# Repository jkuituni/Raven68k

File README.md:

# Raven68k
Raven 68k is a simple Motorola 68k family based single board computer. The machine will serve as a learning tool
for building a 68k based machines for learning on how to interface various chips and add on expansions for the
architecture. It is also aimed to be a platform for learning on how to write firmware and operating system level
code and how to implement the required logic in VHDL code to tie in all of the functionality required. We are
interested on eventually getting Linux up and running on the hardware as the Linux/m68k is still maintained and
it supports many of the basic building blocks.

The project will be documented to a blog along with datasheets of all the components used.

## Folder Structure
*datasheets/* -- The datasheets of the components used in various revisions of Raven.

*firmware/* - ROM images to boot and initialize the system.

*software/* - S68 programs that can be loaded from the firmware. Many of these are built with [EASy68k](http://easy68k.com/).

*hardware/* -- KiCAD schematics and other files as well as VHDL code for the CPLD are located here.

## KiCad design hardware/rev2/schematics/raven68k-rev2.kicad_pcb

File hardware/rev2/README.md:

# Raven68k - Revision 2

The specifications for the revision 2 version of Raven68k are as follows:

- Motorola 68010 CPU
- 64kB of EEPROM for bootstrapping the Linux
- Single 72pin SIMM socket for RAM. Upto 16MB supported.
- Motorola 68681 DUART with USB adapter on one UART and max233 on other
- Dallas DS12887A Real Time Clock
- Xilinx XC9572XL CPLD as system glue logic.

The revision 2 of Raven is intended as a minor improvement and bug fix version. Most likely no further revisions will be made and work will continue in a higher spec follow-up computer.

## Folder structure

*schematic/* - KiCad schematics for this revision.

*vhdl/* - The VHDL source for the CPLD that manages most of the TTL logic present and implements the DRAM controller. 

*xilinx/* - The ISE WebPack (14.2) project itself, which targets a QFP100 XC9572XL.

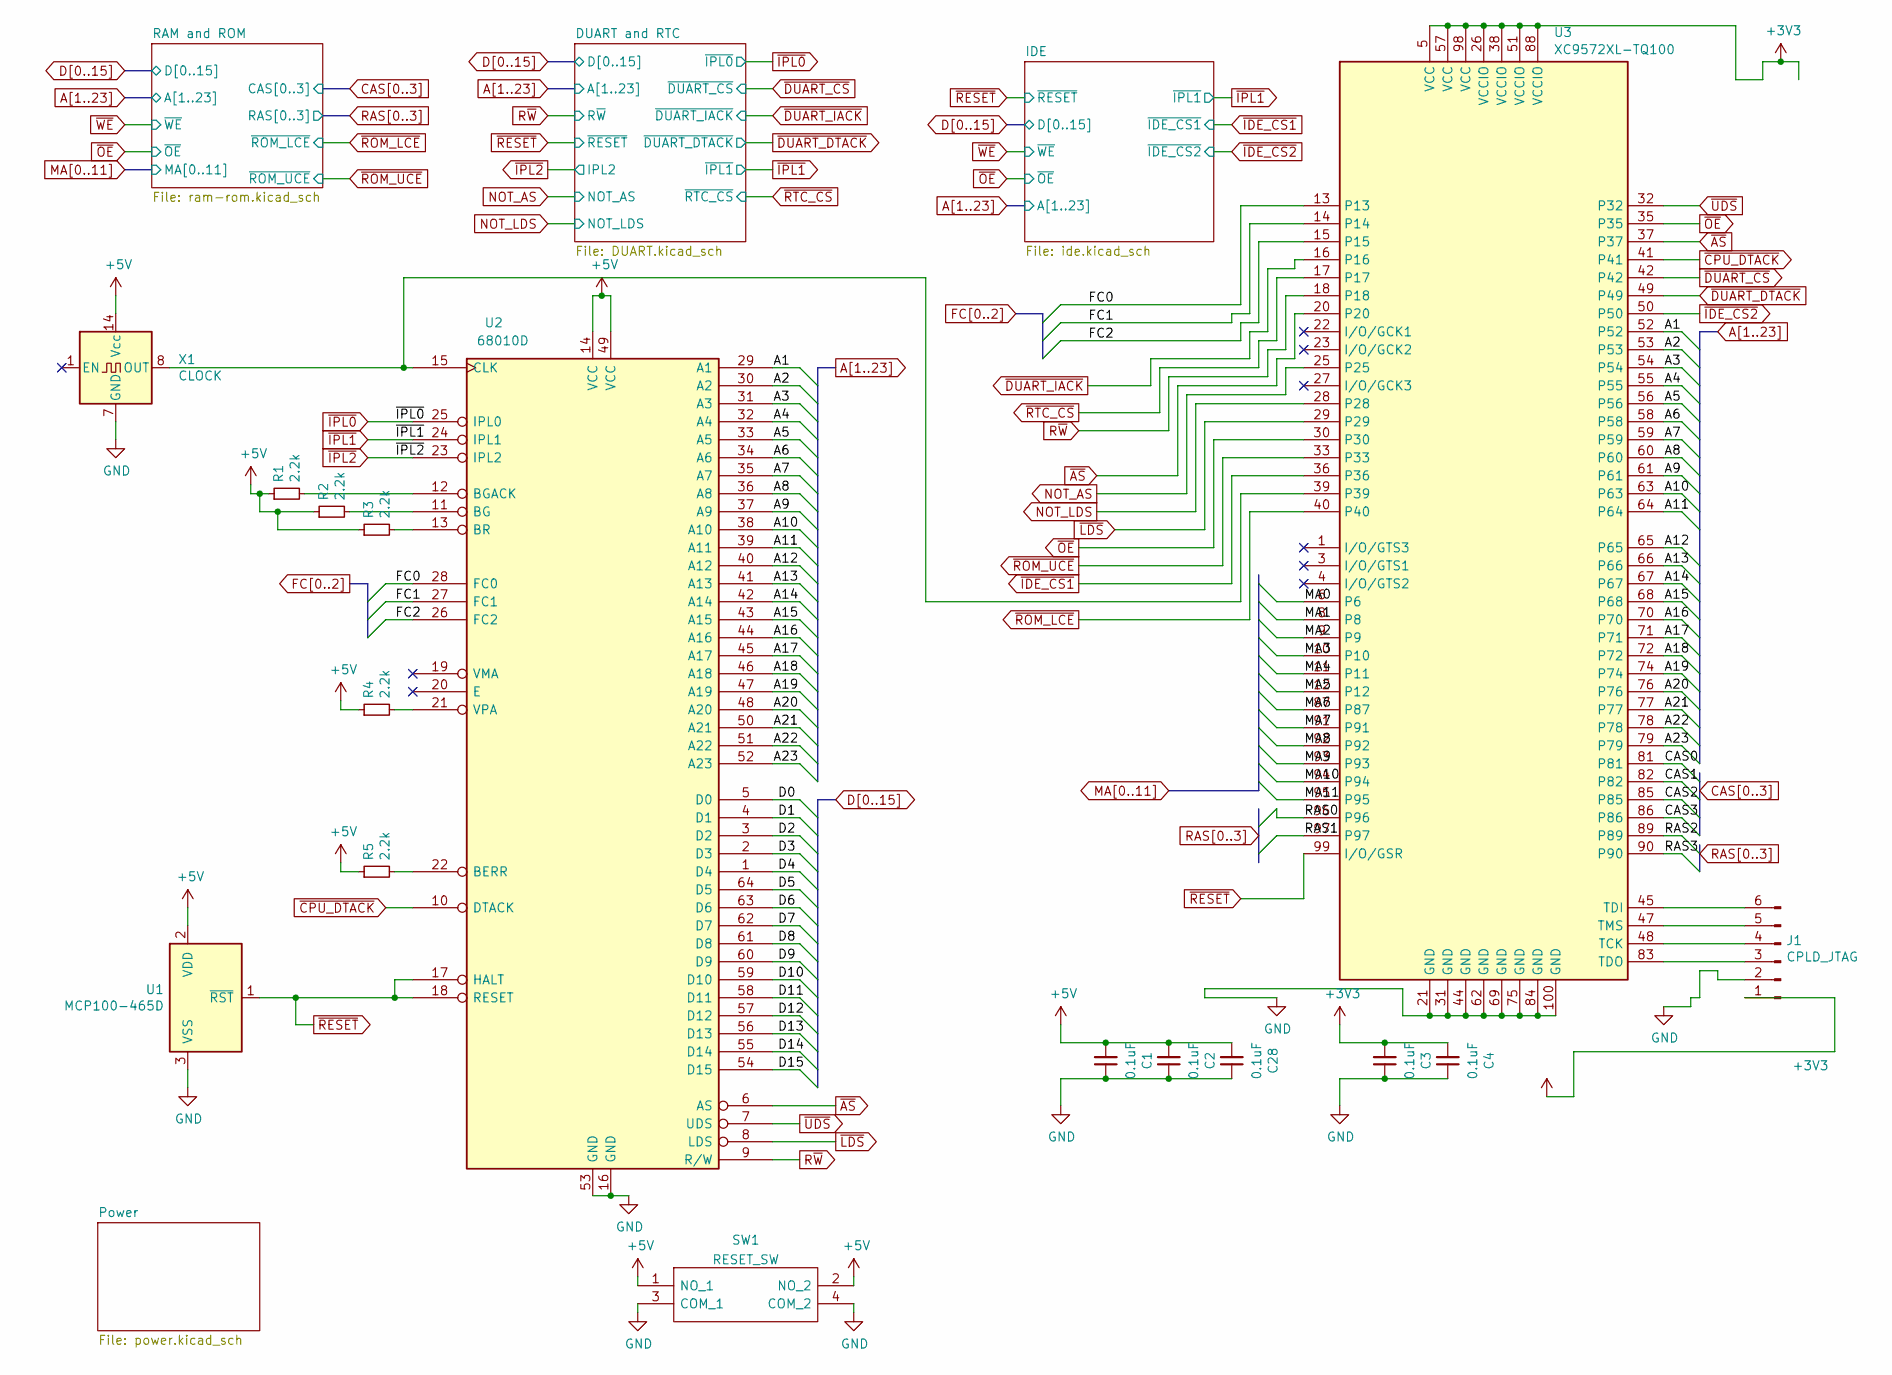
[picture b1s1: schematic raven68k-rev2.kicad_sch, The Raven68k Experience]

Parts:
C1, C2, C3, C4, C28: 0.1uF; C_1206_3216Metric_Pad1.33x1.80mm_HandSolder; LCSC C24497
J1: CPLD_JTAG; PinHeader_1x06_P2.54mm_Vertical
R1, R2, R3, R4, R5: 2.2k; R_1206_3216Metric_Pad1.30x1.75mm_HandSolder
SW1: RESET_SW; TS0266170BK160SCRD; Manufacturer_Part_Number TS02-66-170-BK-160-SCR-D
U1: MCP100-465D; TO-92L_HandSolder
U2: 68010D; DIP-64_W25.4mm_Socket_LongPads
U3: XC9572XL-TQ100; TQFP-100_14x14mm_P0.5mm
X1: CLOCK; Oscillator_DIP-14_LargePads

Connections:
+3V3: C3.2, C4.2, J1.1, U3.5 (VCC), U3.26 (VCCIO), U3.38 (VCCIO), U3.51 (VCCIO), U3.57 (VCC), U3.88 (VCCIO), U3.98 (VCC); also elsewhere on the board
+5V: C1.2, C2.2, C28.2, R1.1, R2.1, R3.1, R4.1, R5.1, SW1.1 (NO_1), SW1.2 (NO_2), U1.2 (VDD), U2.14 (VCC), U2.49 (VCC), X1.14 (Vcc); also elsewhere on the board
A1: U2.29 (A1), U3.52; also elsewhere on the board
A2: U2.30 (A2), U3.53; also elsewhere on the board
A3: U2.31 (A3), U3.54; also elsewhere on the board
A4: U2.32 (A4), U3.55; also elsewhere on the board
A5: U2.33 (A5), U3.56; also elsewhere on the board
A6: U2.34 (A6), U3.58; also elsewhere on the board
A7: U2.35 (A7), U3.59; also elsewhere on the board
A8: U2.36 (A8), U3.60; also elsewhere on the board
A9: U2.37 (A9), U3.61; also elsewhere on the board
A10: U2.38 (A10), U3.63; also elsewhere on the board
A11: U2.39 (A11), U3.64; also elsewhere on the board
A12: U2.40 (A12), U3.65; also elsewhere on the board
A13: U2.41 (A13), U3.66; also elsewhere on the board
A14: U2.42 (A14), U3.67; also elsewhere on the board
A15: U2.43 (A15), U3.68; also elsewhere on the board
A16: U2.44 (A16), U3.70
A17: U2.45 (A17), U3.71
A18: U2.46 (A18), U3.72
A19: U2.47 (A19), U3.74
A20: U2.48 (A20), U3.76
A21: U2.50 (A21), U3.77
A22: U2.51 (A22), U3.78
A23: U2.52 (A23), U3.79
CAS0: U3.81; also elsewhere on the board
CAS1: U3.82; also elsewhere on the board
CAS2: U3.85; also elsewhere on the board
CAS3: U3.86; also elsewhere on the board
D0: U2.5 (D0); also elsewhere on the board
D1: U2.4 (D1); also elsewhere on the board
D2: U2.3 (D2); also elsewhere on the board
D3: U2.2 (D3); also elsewhere on the board
D4: U2.1 (D4); also elsewhere on the board
D5: U2.64 (D5); also elsewhere on the board
D6: U2.63 (D6); also elsewhere on the board
D7: U2.62 (D7); also elsewhere on the board
D8: U2.61 (D8); also elsewhere on the board
D9: U2.60 (D9); also elsewhere on the board
D10: U2.59 (D10); also elsewhere on the board
D11: U2.58 (D11); also elsewhere on the board
D12: U2.57 (D12); also elsewhere on the board
D13: U2.56 (D13); also elsewhere on the board
D14: U2.55 (D14); also elsewhere on the board
D15: U2.54 (D15); also elsewhere on the board
FC0: U2.28 (FC0), U3.13
FC1: U2.27 (FC1), U3.14
FC2: U2.26 (FC2), U3.15
GND: C1.1, C2.1, C3.1, C4.1, C28.1, J1.2, SW1.3 (COM_1), SW1.4 (COM_2), U1.3 (VSS), U2.16 (GND), U2.53 (GND), U3.21 (GND), U3.31 (GND), U3.44 (GND), U3.62 (GND), U3.69 (GND), U3.75 (GND), U3.84 (GND), U3.100 (GND), X1.7 (GND); also elsewhere on the board
MA0: U3.6; also elsewhere on the board
MA1: U3.8; also elsewhere on the board
MA2: U3.9; also elsewhere on the board
MA3: U3.10; also elsewhere on the board
MA4: U3.11; also elsewhere on the board
MA5: U3.12; also elsewhere on the board
MA6: U3.87; also elsewhere on the board
MA7: U3.91; also elsewhere on the board
MA8: U3.92; also elsewhere on the board
MA9: U3.93; also elsewhere on the board
MA10: U3.94; also elsewhere on the board
MA11: U3.95; also elsewhere on the board
NOT_AS: U3.25; also elsewhere on the board
NOT_LDS: U3.28; also elsewhere on the board
unnamed: J1.3, U3.83 (TDO)
unnamed: J1.4, U3.48 (TCK)
unnamed: J1.5, U3.47 (TMS)
unnamed: J1.6, U3.45 (TDI)
unnamed: R5.2, U2.22 (BERR)
unnamed: R2.2, U2.11 (BG)
unnamed: R1.2, U2.12 (BGACK)
unnamed: R3.2, U2.13 (BR)
unnamed: U2.15 (CLK), U3.39, X1.8 (OUT)
unnamed: R4.2, U2.21 (VPA)
RAS0: U3.96; also elsewhere on the board
RAS1: U3.97; also elsewhere on the board
RAS2: U3.89; also elsewhere on the board
RAS3: U3.90; also elsewhere on the board
R~W: U2.9 (R/W), U3.18; also elsewhere on the board
~AS: U2.6 (AS), U3.20, U3.37
~CPU_DTACK: U2.10 (DTACK), U3.41
~DUART_CS: U3.42; also elsewhere on the board
~DUART_DTACK: U3.49; also elsewhere on the board
~DUART_IACK: U3.16; also elsewhere on the board
~IDE_CS1: U3.36; also elsewhere on the board
~IDE_CS2: U3.50; also elsewhere on the board
~IPL0: U2.25 (IPL0); also elsewhere on the board
~IPL1: U2.24 (IPL1); also elsewhere on the board
~IPL2: U2.23 (IPL2); also elsewhere on the board
~LDS: U2.8 (LDS), U3.29
~OE: U3.30, U3.35; also elsewhere on the board
~RESET: U1.1 (~RST), U2.17 (HALT), U2.18 (RESET), U3.99 (I/O/GSR); also elsewhere on the board
~ROM_LCE: U3.40; also elsewhere on the board
~ROM_UCE: U3.33; also elsewhere on the board
~RTC_CS: U3.17; also elsewhere on the board
~UDS: U2.7 (UDS), U3.32

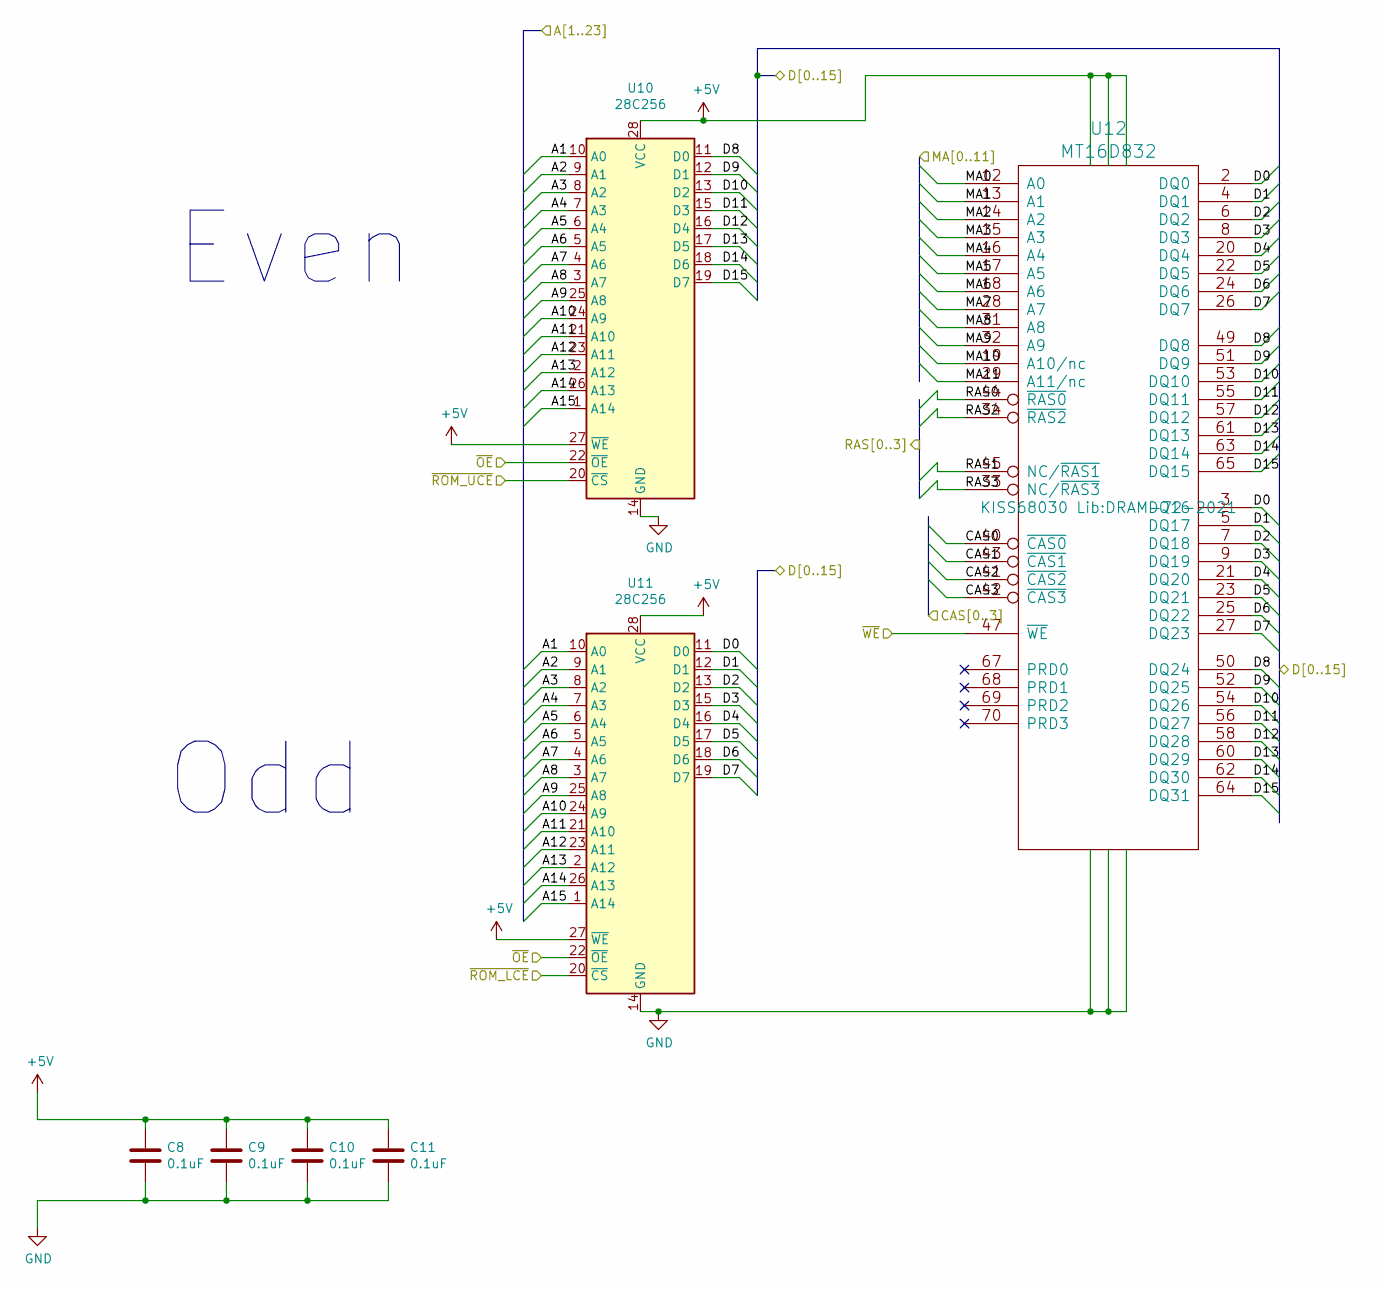
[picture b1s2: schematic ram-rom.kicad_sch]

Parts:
C8, C9, C10, C11: 0.1uF; C_1206_3216Metric_Pad1.33x1.80mm_HandSolder; LCSC C24497
U10, U11: 28C256; DIP-28_W15.24mm_Socket_LongPads
U12: MT16D832; DRAM-72-2021

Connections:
+5V: C8.1, C9.1, C10.1, C11.1, U10.27 (~WE), U10.28 (VCC), U11.27 (~WE), U11.28 (VCC), U12.10 (VCC), U12.30 (VCC), U12.59 (VCC); also elsewhere on the board
A1: U10.10 (A0), U11.10 (A0); also elsewhere on the board
A2: U10.9 (A1), U11.9 (A1); also elsewhere on the board
A3: U10.8 (A2), U11.8 (A2); also elsewhere on the board
A4: U10.7 (A3), U11.7 (A3); also elsewhere on the board
A5: U10.6 (A4), U11.6 (A4); also elsewhere on the board
A6: U10.5 (A5), U11.5 (A5); also elsewhere on the board
A7: U10.4 (A6), U11.4 (A6); also elsewhere on the board
A8: U10.3 (A7), U11.3 (A7); also elsewhere on the board
A9: U10.25 (A8), U11.25 (A8); also elsewhere on the board
A10: U10.24 (A9), U11.24 (A9); also elsewhere on the board
A11: U10.21 (A10), U11.21 (A10); also elsewhere on the board
A12: U10.23 (A11), U11.23 (A11); also elsewhere on the board
A13: U10.2 (A12), U11.2 (A12); also elsewhere on the board
A14: U10.26 (A13), U11.26 (A13); also elsewhere on the board
A15: U10.1 (A14), U11.1 (A14); also elsewhere on the board
CAS0: U12.40 (~CAS0); also elsewhere on the board
CAS1: U12.43 (~CAS1); also elsewhere on the board
CAS2: U12.41 (~CAS2); also elsewhere on the board
CAS3: U12.42 (~CAS3); also elsewhere on the board
D0: U11.11 (D0), U12.2 (DQ0), U12.3 (DQ16); also elsewhere on the board
D1: U11.12 (D1), U12.4 (DQ1), U12.5 (DQ17); also elsewhere on the board
D2: U11.13 (D2), U12.6 (DQ2), U12.7 (DQ18); also elsewhere on the board
D3: U11.15 (D3), U12.8 (DQ3), U12.9 (DQ19); also elsewhere on the board
D4: U11.16 (D4), U12.20 (DQ4), U12.21 (DQ20); also elsewhere on the board
D5: U11.17 (D5), U12.22 (DQ5), U12.23 (DQ21); also elsewhere on the board
D6: U11.18 (D6), U12.24 (DQ6), U12.25 (DQ22); also elsewhere on the board
D7: U11.19 (D7), U12.26 (DQ7), U12.27 (DQ23); also elsewhere on the board
D8: U10.11 (D0), U12.49 (DQ8), U12.50 (DQ24); also elsewhere on the board
D9: U10.12 (D1), U12.51 (DQ9), U12.52 (DQ25); also elsewhere on the board
D10: U10.13 (D2), U12.53 (DQ10), U12.54 (DQ26); also elsewhere on the board
D11: U10.15 (D3), U12.55 (DQ11), U12.56 (DQ27); also elsewhere on the board
D12: U10.16 (D4), U12.57 (DQ12), U12.58 (DQ28); also elsewhere on the board
D13: U10.17 (D5), U12.60 (DQ29), U12.61 (DQ13); also elsewhere on the board
D14: U10.18 (D6), U12.62 (DQ30), U12.63 (DQ14); also elsewhere on the board
D15: U10.19 (D7), U12.64 (DQ31), U12.65 (DQ15); also elsewhere on the board
GND: C8.2, C9.2, C10.2, C11.2, U10.14 (GND), U11.14 (GND), U12.1 (GND), U12.39 (GND), U12.72 (GND); also elsewhere on the board
MA0: U12.12 (A0); also elsewhere on the board
MA1: U12.13 (A1); also elsewhere on the board
MA2: U12.14 (A2); also elsewhere on the board
MA3: U12.15 (A3); also elsewhere on the board
MA4: U12.16 (A4); also elsewhere on the board
MA5: U12.17 (A5); also elsewhere on the board
MA6: U12.18 (A6); also elsewhere on the board
MA7: U12.28 (A7); also elsewhere on the board
MA8: U12.31 (A8); also elsewhere on the board
MA9: U12.32 (A9); also elsewhere on the board
MA10: U12.19 (A10/nc); also elsewhere on the board
MA11: U12.29 (A11/nc); also elsewhere on the board
RAS0: U12.44 (~RAS0); also elsewhere on the board
RAS1: U12.45 (NC/~RAS1); also elsewhere on the board
RAS2: U12.34 (~RAS2); also elsewhere on the board
RAS3: U12.33 (NC/~RAS3); also elsewhere on the board
~OE: U10.22 (~OE), U11.22 (~OE); also elsewhere on the board
~ROM_LCE: U11.20 (~CS); also elsewhere on the board
~ROM_UCE: U10.20 (~CS); also elsewhere on the board
~WE: U12.47 (~WE); also elsewhere on the board

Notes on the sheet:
Even
Odd

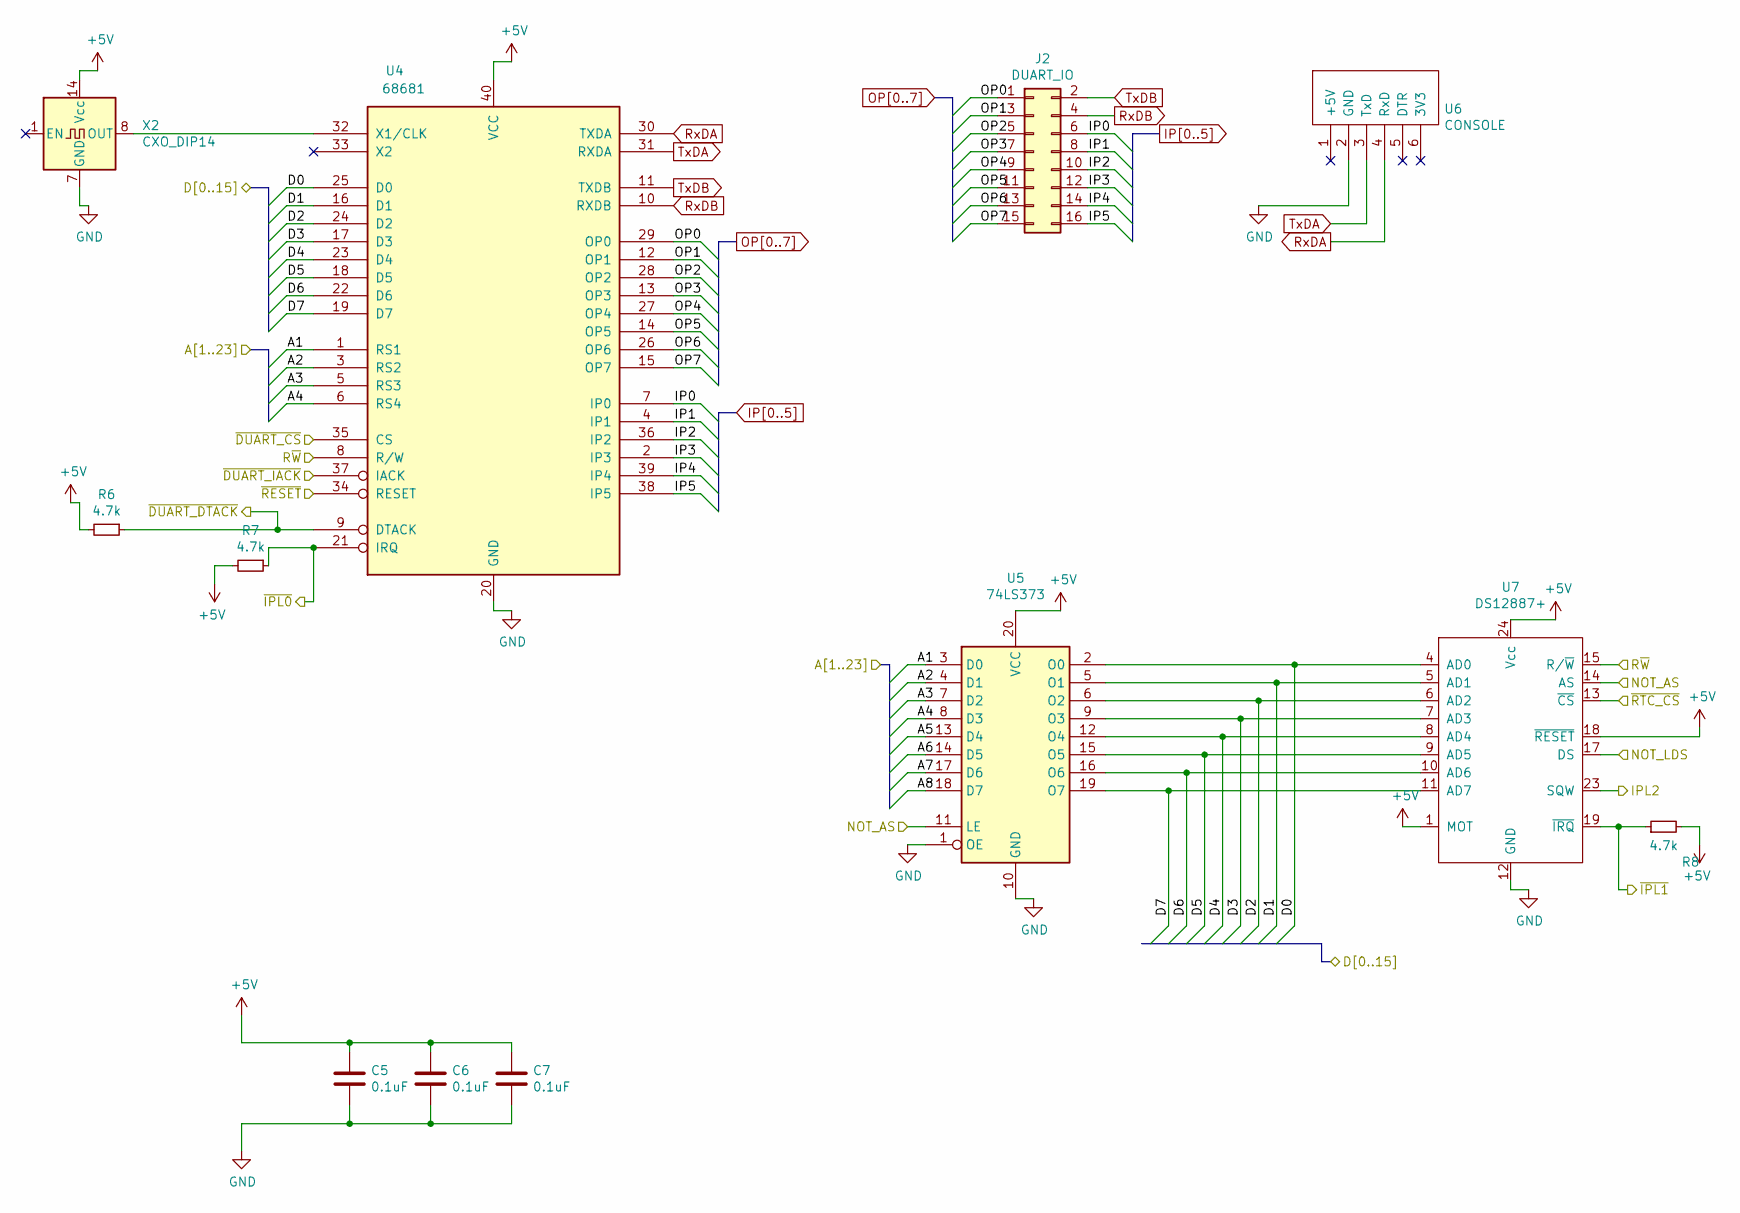
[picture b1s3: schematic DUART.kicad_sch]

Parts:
C5, C6, C7: 0.1uF; C_1206_3216Metric_Pad1.33x1.80mm_HandSolder; LCSC C24497
J2: DUART_IO; PinHeader_2x08_P2.54mm_Vertical
R6, R7, R8: 4.7k; R_1206_3216Metric_Pad1.30x1.75mm_HandSolder
U4: 68681; DIP-40_W25.4mm_Socket_LongPads
U5: 74LS373; DIP-20_W7.62mm_Socket_LongPads
U6: CONSOLE; PinHeader_1x06_P2.54mm_Vertical
U7: DS12887+; DIP-24_W15.24mm_Socket_LongPads
X2: CXO_DIP14; Oscillator_DIP-14_LargePads

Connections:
+5V: C5.1, C6.1, C7.1, R6.2, R7.2, R8.2, U4.40 (VCC), U5.20 (VCC), U7.1 (MOT), U7.18 (~RESET), U7.24 (Vcc), X2.14 (Vcc); also elsewhere on the board
A1: U4.1 (RS1), U5.3 (D0); also elsewhere on the board
A2: U4.3 (RS2), U5.4 (D1); also elsewhere on the board
A3: U4.5 (RS3), U5.7 (D2); also elsewhere on the board
A4: U4.6 (RS4), U5.8 (D3); also elsewhere on the board
A5: U5.13 (D4); also elsewhere on the board
A6: U5.14 (D5); also elsewhere on the board
A7: U5.17 (D6); also elsewhere on the board
A8: U5.18 (D7); also elsewhere on the board
D0: U4.25 (D0), U5.2 (O0), U7.4 (AD0); also elsewhere on the board
D1: U4.16 (D1), U5.5 (O1), U7.5 (AD1); also elsewhere on the board
D2: U4.24 (D2), U5.6 (O2), U7.6 (AD2); also elsewhere on the board
D3: U4.17 (D3), U5.9 (O3), U7.7 (AD3); also elsewhere on the board
D4: U4.23 (D4), U5.12 (O4), U7.8 (AD4); also elsewhere on the board
D5: U4.18 (D5), U5.15 (O5), U7.9 (AD5); also elsewhere on the board
D6: U4.22 (D6), U5.16 (O6), U7.10 (AD6); also elsewhere on the board
D7: U4.19 (D7), U5.19 (O7), U7.11 (AD7); also elsewhere on the board
GND: C5.2, C6.2, C7.2, U4.20 (GND), U5.1 (OE), U5.10 (GND), U6.2 (GND), U7.12 (GND), X2.7 (GND); also elsewhere on the board
IP0: J2.6, U4.7 (IP0)
IP1: J2.8, U4.4 (IP1)
IP2: J2.10, U4.36 (IP2)
IP3: J2.12, U4.2 (IP3)
IP4: J2.14, U4.39 (IP4)
IP5: J2.16, U4.38 (IP5)
NOT_AS: U5.11 (LE), U7.14 (AS); also elsewhere on the board
NOT_LDS: U7.17 (DS); also elsewhere on the board
unnamed: U4.32 (X1/CLK), X2.8 (OUT)
OP0: J2.1, U4.29 (OP0)
OP1: J2.3, U4.12 (OP1)
OP2: J2.5, U4.28 (OP2)
OP3: J2.7, U4.13 (OP3)
OP4: J2.9, U4.27 (OP4)
OP5: J2.11, U4.14 (OP5)
OP6: J2.13, U4.26 (OP6)
OP7: J2.15, U4.15 (OP7)
RxDA: U4.30 (TXDA), U6.4 (RxD)
RxDB: J2.4, U4.10 (RXDB)
R~W: U4.8 (R/W), U7.15 (R/~W); also elsewhere on the board
TxDA: U4.31 (RXDA), U6.3 (TxD)
TxDB: J2.2, U4.11 (TXDB)
~DUART_CS: U4.35 (CS); also elsewhere on the board
~DUART_DTACK: R6.1, U4.9 (DTACK); also elsewhere on the board
~DUART_IACK: U4.37 (IACK); also elsewhere on the board
~IPL0: R7.1, U4.21 (IRQ); also elsewhere on the board
~IPL1: R8.1, U7.19 (~IRQ); also elsewhere on the board
~IPL2: U7.23 (SQW); also elsewhere on the board
~RESET: U4.34 (RESET); also elsewhere on the board
~RTC_CS: U7.13 (~CS); also elsewhere on the board

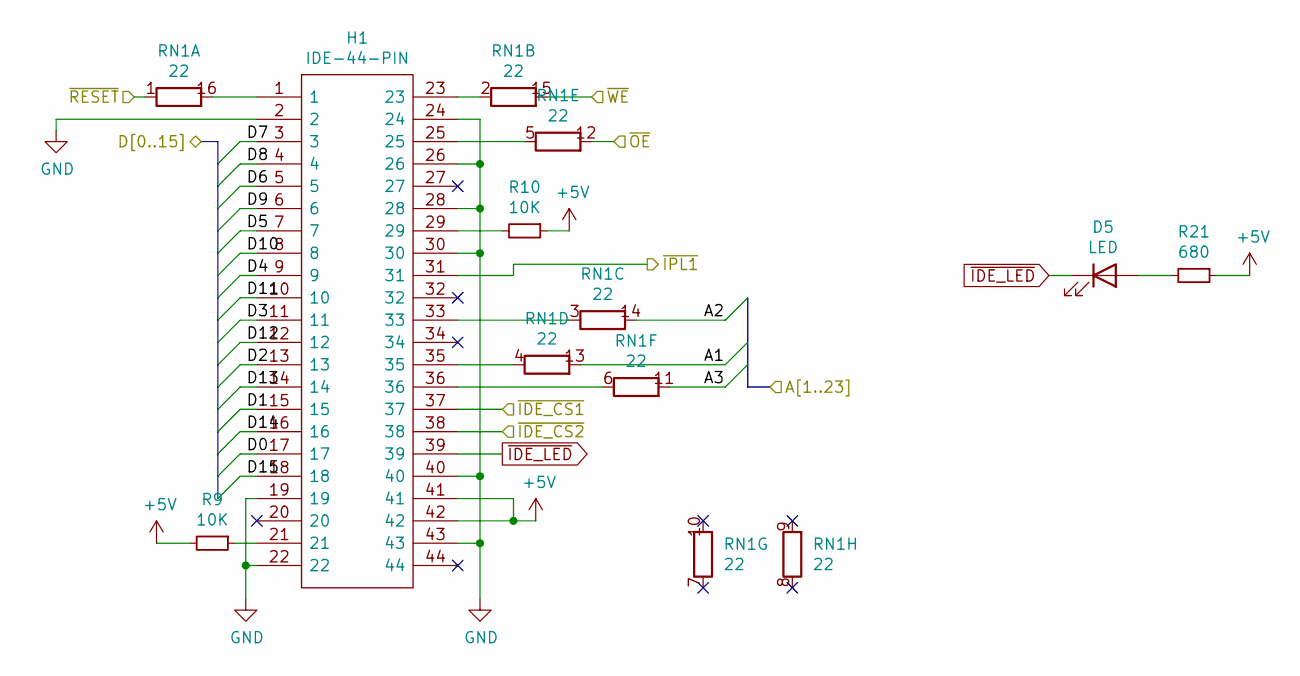
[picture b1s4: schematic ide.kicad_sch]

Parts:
D5: LED; LED_D3.0mm
H1: IDE-44-PIN; SHDR44W55P200_2X22_4665X630X640P; Manufacturer_Part_Number 57102-G06-22LF
R9, R10: 10K; R_1206_3216Metric_Pad1.30x1.75mm_HandSolder
R21: 680; R_1206_3216Metric_Pad1.30x1.75mm_HandSolder
RN1: 22; DIP-16_W7.62mm_Socket_LongPads

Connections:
+5V: H1.41, H1.42, R9.2, R10.1, R21.1; also elsewhere on the board
A1: RN1.13 (R4.2); also elsewhere on the board
A2: RN1.14 (R3.2); also elsewhere on the board
A3: RN1.11 (R6.2); also elsewhere on the board
D0: H1.17; also elsewhere on the board
D1: H1.15; also elsewhere on the board
D2: H1.13; also elsewhere on the board
D3: H1.11; also elsewhere on the board
D4: H1.9; also elsewhere on the board
D5: H1.7; also elsewhere on the board
D6: H1.5; also elsewhere on the board
D7: H1.3; also elsewhere on the board
D8: H1.4; also elsewhere on the board
D9: H1.6; also elsewhere on the board
D10: H1.8; also elsewhere on the board
D11: H1.10; also elsewhere on the board
D12: H1.12; also elsewhere on the board
D13: H1.14; also elsewhere on the board
D14: H1.16; also elsewhere on the board
D15: H1.18; also elsewhere on the board
GND: H1.2, H1.19, H1.22, H1.24, H1.26, H1.28, H1.30, H1.40, H1.43; also elsewhere on the board
unnamed: D5.2 (A), R21.2
unnamed: H1.21, R9.1
unnamed: H1.29, R10.2
unnamed: H1.1, RN1.16 (R1.2)
unnamed: H1.23, RN1.2 (R2.1)
unnamed: H1.33, RN1.3 (R3.1)
unnamed: H1.35, RN1.4 (R4.1)
unnamed: H1.25, RN1.5 (R5.1)
unnamed: H1.36, RN1.6 (R6.1)
~IDE_CS1: H1.37; also elsewhere on the board
~IDE_CS2: H1.38; also elsewhere on the board
~IDE_LED: D5.1 (K), H1.39
~IPL1: H1.31; also elsewhere on the board
~OE: RN1.12 (R5.2); also elsewhere on the board
~RESET: RN1.1 (R1.1); also elsewhere on the board
~WE: RN1.15 (R2.2); also elsewhere on the board

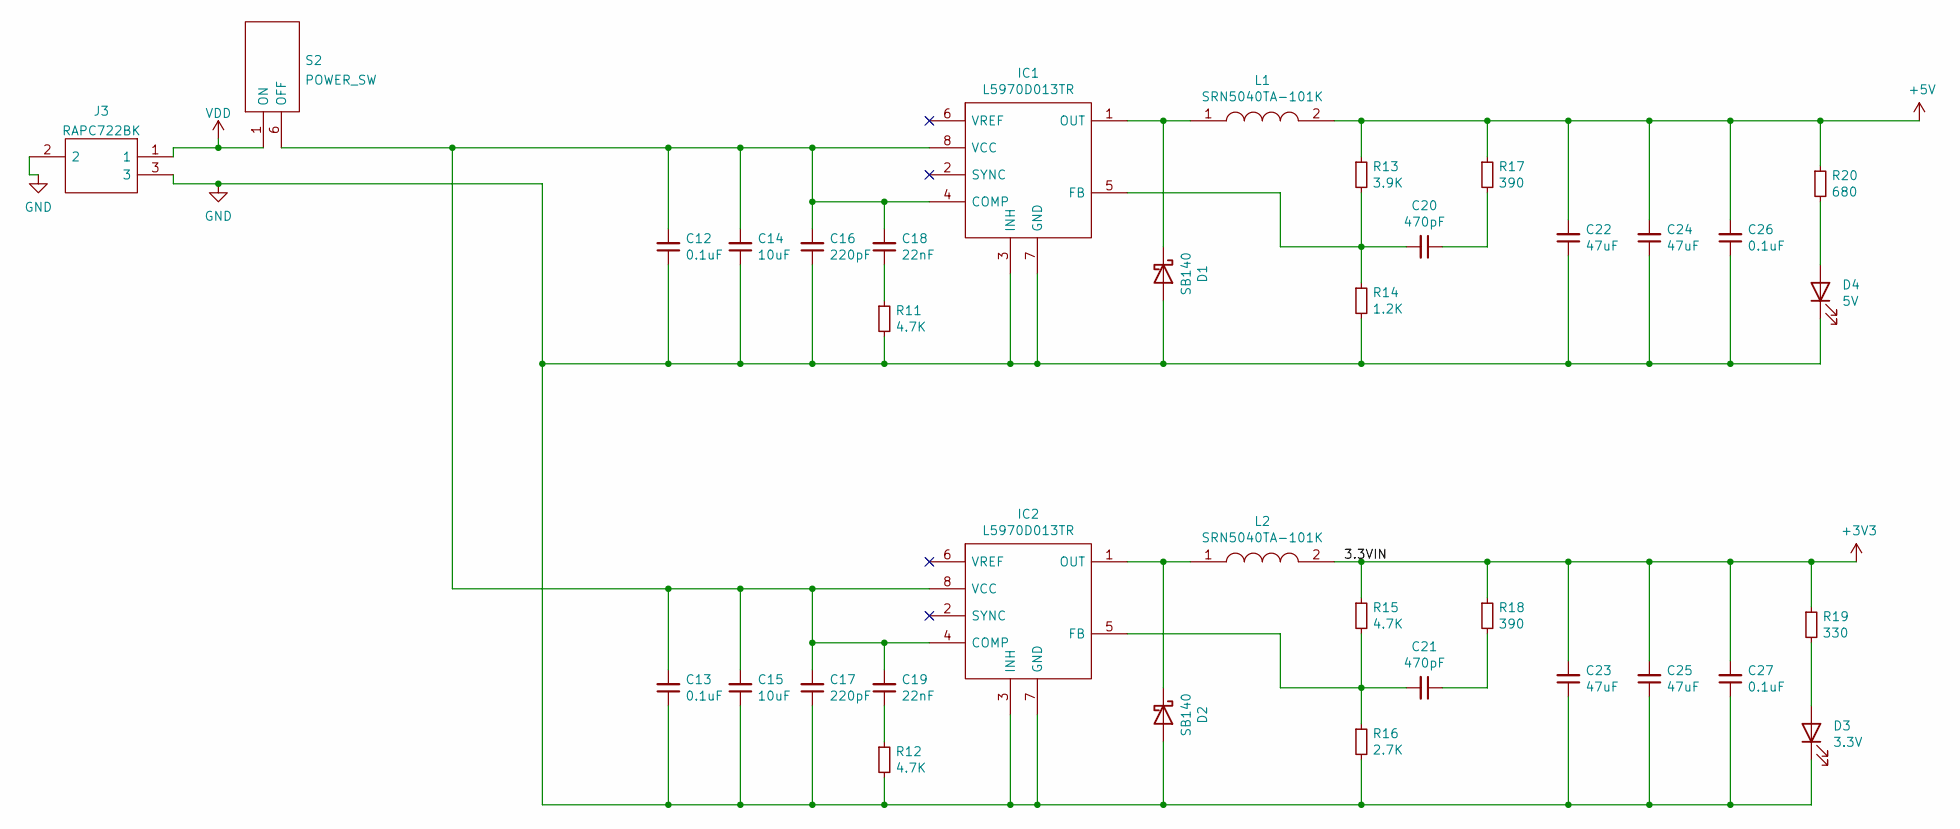
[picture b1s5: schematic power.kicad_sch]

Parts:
C12, C13, C26, C27: 0.1uF; C_1206_3216Metric_Pad1.33x1.80mm_HandSolder; LCSC C24497
C14, C15: 10uF; C_1206_3216Metric_Pad1.33x1.80mm_HandSolder; LCSC C13585
C16, C17: 220pF; C_1206_3216Metric_Pad1.33x1.80mm_HandSolder; LCSC C1854
C18, C19: 22nF; C_1206_3216Metric_Pad1.33x1.80mm_HandSolder; LCSC C97929
C20, C21: 470pF; C_1206_3216Metric_Pad1.33x1.80mm_HandSolder; LCSC C1868
C22, C23, C24, C25: 47uF; C_1206_3216Metric_Pad1.33x1.80mm_HandSolder
D1, D2: SB140; D_1206_3216Metric_Pad1.42x1.75mm_HandSolder
D3: 3.3V; LED_D3.0mm
D4: 5V; LED_D3.0mm
IC1, IC2: L5970D013TR; SO-8_5.3x6.2mm_P1.27mm; Manufacturer_Part_Number L5970D013TR; Mouser Part Number 511-L5970D013TR
J3: RAPC722BK; Manufacturer_Part_Number RAPC722BK; Mouser Part Number 502-RAPC722BK
L1, L2: SRN5040TA-101K; SRN5040TA101K; Manufacturer_Part_Number SRN5040TA-101K; Mouser Part Number 652-SRN5040TA-101K
R11, R12: 4.7K; R_1206_3216Metric_Pad1.30x1.75mm_HandSolder; LCSC C17936
R13: 3.9K; R_1206_3216Metric_Pad1.30x1.75mm_HandSolder
R14: 1.2K; R_1206_3216Metric_Pad1.30x1.75mm_HandSolder
R15: 4.7K; R_1206_3216Metric_Pad1.30x1.75mm_HandSolder
R16: 2.7K; R_1206_3216Metric_Pad1.30x1.75mm_HandSolder
R17, R18: 390; R_1206_3216Metric_Pad1.30x1.75mm_HandSolder
R19: 330; R_1206_3216Metric_Pad1.30x1.75mm_HandSolder
R20: 680; R_1206_3216Metric_Pad1.30x1.75mm_HandSolder
S2: POWER_SW; GPTS203212B; Manufacturer_Part_Number GPTS203212B; Mouser Part Number 629-GPTS203212B

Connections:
+3V3: C23.2, C25.2, C27.2, L2.2, R15.1, R18.1, R19.1; also elsewhere on the board
+5V: C22.2, C24.2, C26.2, L1.2, R13.1, R17.1, R20.1; also elsewhere on the board
GND: C12.1, C13.1, C14.1, C15.1, C16.1, C17.1, C22.1, C23.1, C24.1, C25.1, C26.1, C27.1, D1.2 (A), D2.2 (A), D3.1 (K), D4.1 (K), IC1.3 (INH), IC1.7 (GND), IC2.3 (INH), IC2.7 (GND), J3.2, J3.3, R11.2, R12.2, R14.2, R16.2; also elsewhere on the board
unnamed: C18.1, R11.1
unnamed: C19.1, R12.1
unnamed: C20.1, R17.2
unnamed: C21.1, R18.2
unnamed: D1.1 (K), IC1.1 (OUT), L1.1
unnamed: D2.1 (K), IC2.1 (OUT), L2.1
unnamed: D3.2 (A), R19.2
unnamed: D4.2 (A), R20.2
unnamed: C12.2, C13.2, C14.2, C15.2, C16.2, C17.2, C18.2, C19.2, IC1.4 (COMP), IC1.8 (VCC), IC2.4 (COMP), IC2.8 (VCC), S2.6 (OFF)
unnamed: C20.2, IC1.5 (FB), R13.2, R14.1
unnamed: C21.2, IC2.5 (FB), R15.2, R16.1
VDD: J3.1, S2.1 (ON)

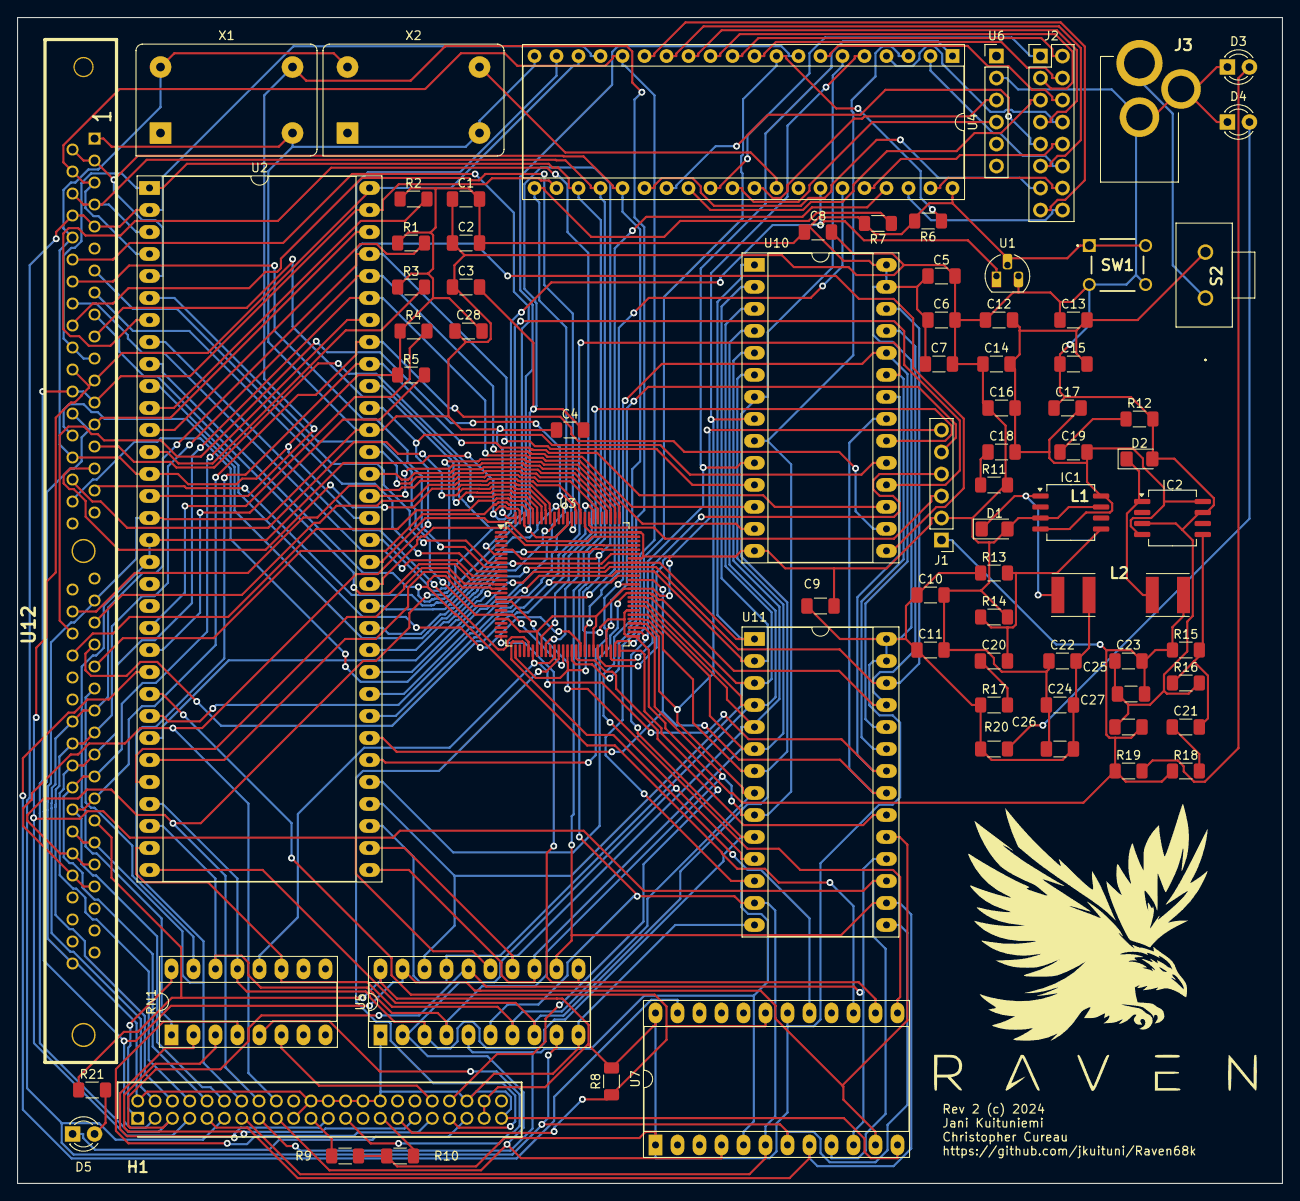
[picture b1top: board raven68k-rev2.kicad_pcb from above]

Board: 2 copper layers, 146.0 x 134.6 mm, 77 parts (0 on the bottom side), 137 nets.

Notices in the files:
hardware/rev2/schematics/raven68k-rev2.kicad_pcb:
Rev 2 (c) 2024
prototypes/v1/raven-prototypes.kicad_pcb:
(C) 2018 Chris Cureau and Jani Kuituniemi
parts and their libraries:
Copyright 2016 Accelerated Designs. All rights reserved.
